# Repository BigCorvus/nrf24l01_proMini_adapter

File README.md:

# nrf24l01_proMini_adapter
Connects tiny nrf42l01+ transceiver boards with Arduino Pro Mini boards.
See http://www.thinkering.de/cms/?p=687 for more info.

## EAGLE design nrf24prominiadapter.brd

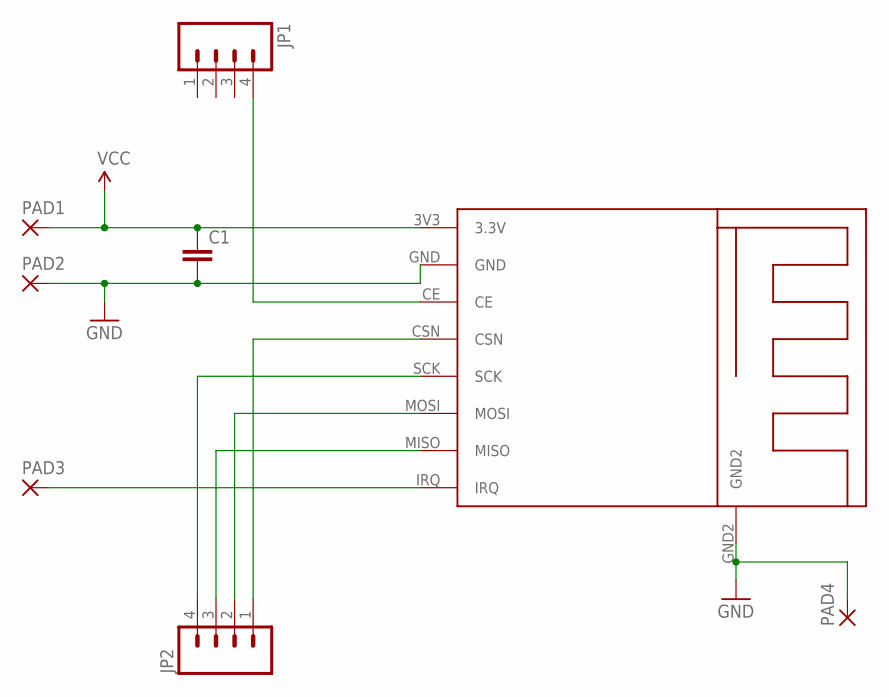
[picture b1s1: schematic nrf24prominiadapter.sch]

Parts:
C1: C-EUC0805; C0805
JP1, JP2: M04NO_SILK_ALL_ROUND; 1X04_NO_SILK_ALL_ROUND
PAD1, PAD2, PAD3, PAD4: SMD2; SMD1,27-2,54
U$1: NRF24MINI

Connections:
GND: C1.2, PAD2.1, PAD4.1, U$1.GND, U$1.GND2
unnamed: JP1.4, U$1.CE
unnamed: JP2.1, U$1.CSN
unnamed: JP2.4, U$1.SCK
unnamed: JP2.2, U$1.MOSI
unnamed: JP2.3, U$1.MISO
unnamed: PAD3.1, U$1.IRQ
VCC: C1.1, PAD1.1, U$1.3V3 (3.3V)

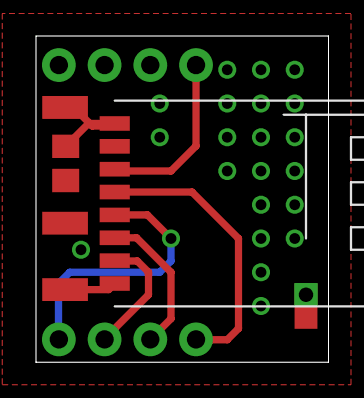
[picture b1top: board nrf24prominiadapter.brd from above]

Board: 2 copper layers, 16.2 x 18.1 mm, 8 parts (0 on the bottom side), 8 nets.

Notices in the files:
parts and their libraries:
SparkFun-Connectors: Licensing: Creative Commons ShareAlike 4.0 International - https://creativecommons.org/licenses/by-sa/4.0
